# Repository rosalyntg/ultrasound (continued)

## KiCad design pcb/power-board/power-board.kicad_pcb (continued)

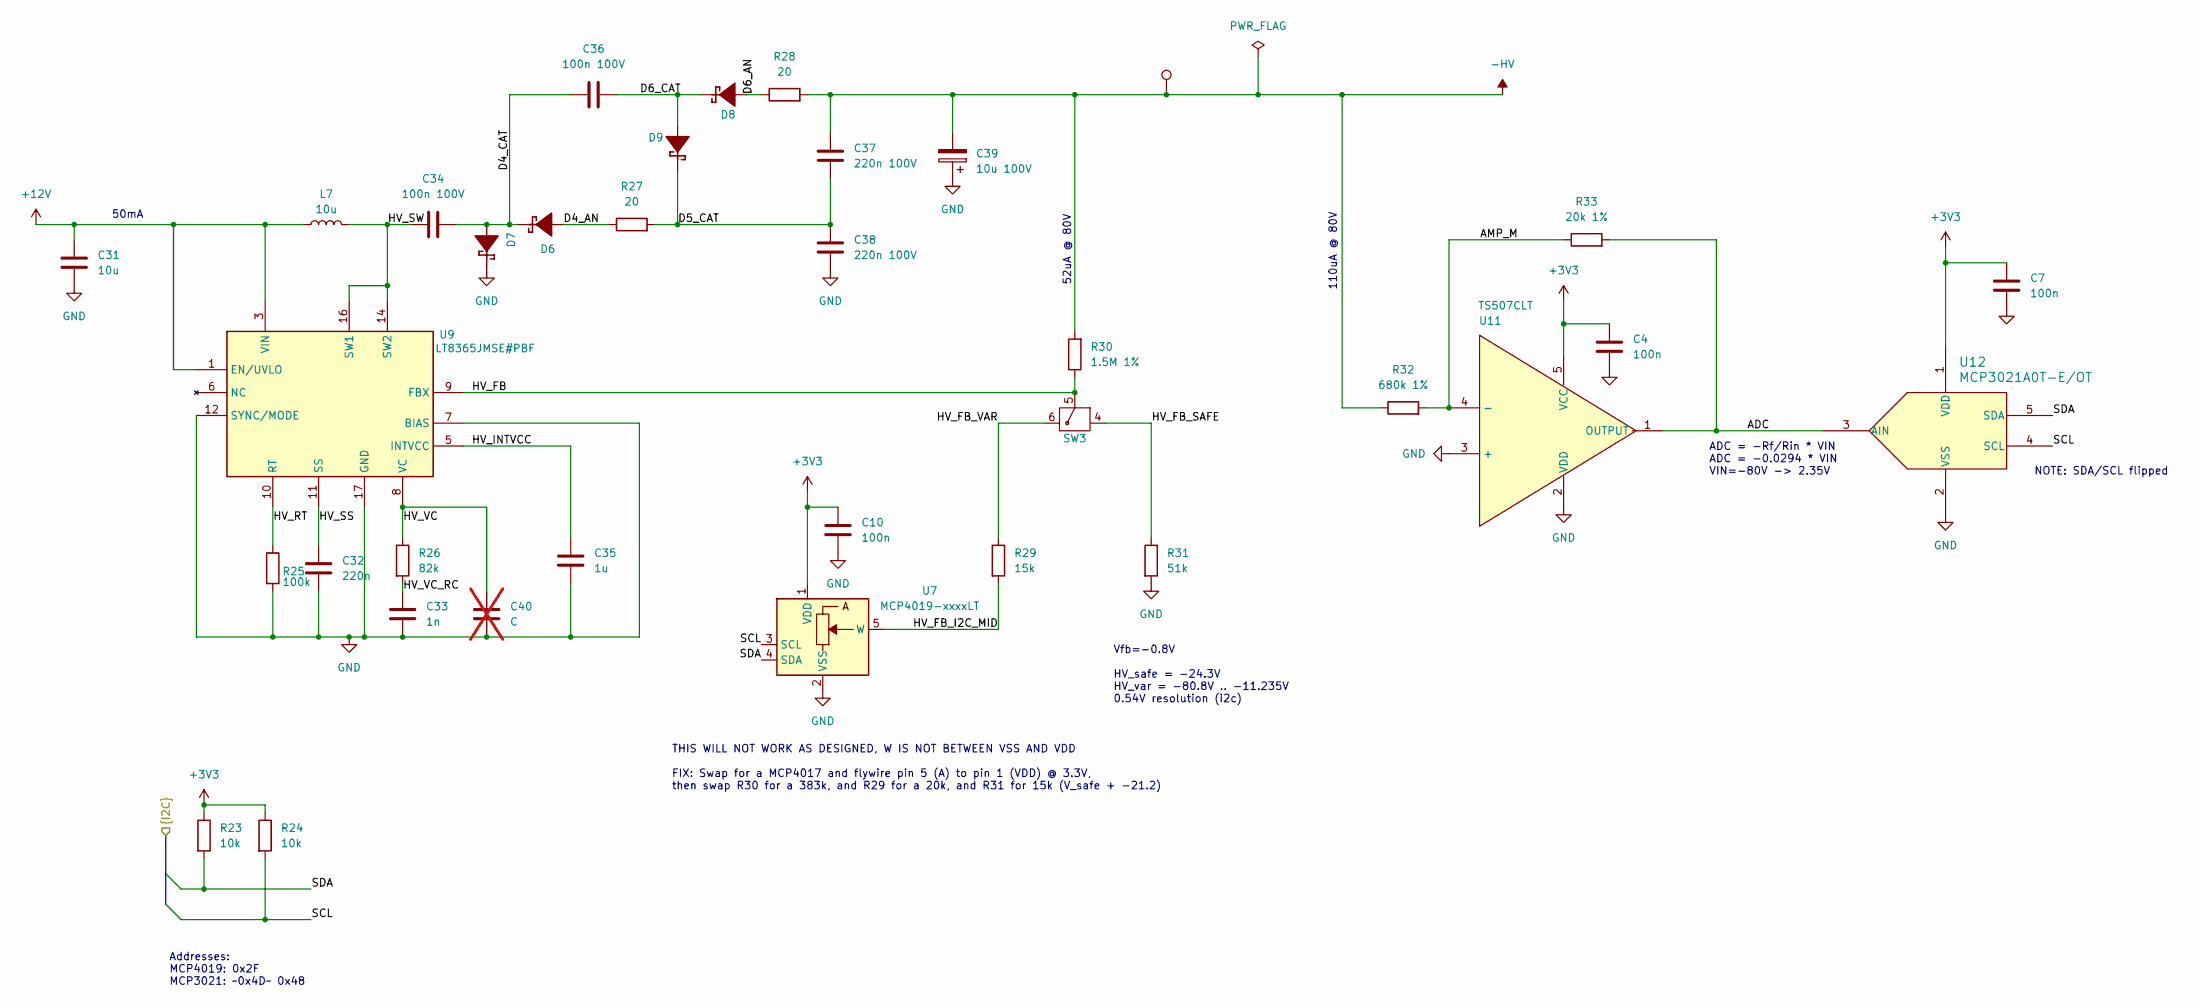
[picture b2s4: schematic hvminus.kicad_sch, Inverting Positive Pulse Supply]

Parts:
C4, C7, C10: 100n; C_0805_2012Metric_Pad1.18x1.45mm_HandSolder; Voltage Rating 25V; Manufacturer_Part_Number GCM21BR71E104KA37L; DigiKey Part Number 490-14779-1-ND
C31: 10u; C_0805_2012Metric_Pad1.18x1.45mm_HandSolder; Voltage Rating 25V; Manufacturer_Part_Number GRM21BR61E106KA73K; DigiKey Part Number 490-16824-2-ND
C32: 220n; C_0805_2012Metric_Pad1.18x1.45mm_HandSolder; Voltage Rating 25V; Manufacturer_Part_Number GRM219R71E224KA01D; DigiKey Part Number 490-1675-2-ND
C33: 1n; C_0805_2012Metric_Pad1.18x1.45mm_HandSolder; Voltage Rating 50V; Manufacturer_Part_Number GRM216R71H102KA01D
C34, C36: 100n 100V; C_0805_2012Metric_Pad1.18x1.45mm_HandSolder; Voltage Rating 100V; Manufacturer_Part_Number GCM21BR72A104KA37L; DigiKey Part Number 490-4789-1-ND
C35: 1u; C_0805_2012Metric_Pad1.18x1.45mm_HandSolder; Voltage Rating 10V; Manufacturer_Part_Number GRM21BR71A105KA01L
C37, C38: 220n 100V; C_1210_3225Metric_Pad1.33x2.70mm_HandSolder; Voltage Rating 200V; Manufacturer_Part_Number GRM32DR72D224KW01L; DigiKey Part Number 490-13380-1-ND
C39: 10u 100V; CP_Radial_D10.0mm_P5.00mm; Voltage Rating 200V; Manufacturer_Part_Number ECA-2DHG100; DigiKey Part Number P19449-ND
C40: C; C_0805_2012Metric_Pad1.18x1.45mm_HandSolder; not fitted
D6, D7, D8, D9: SMD1150PL-TP; SMD1150PL; Voltage Rating 150V; Mouser Part Number 621-DFLS1150-7
L7: 10u; WURTH_WE-LHMI-4.45mm; Mouser Part Number 710-74437324100
R23, R24: 10k; R_0805_2012Metric_Pad1.20x1.40mm_HandSolder; Manufacturer_Part_Number RC0805JR-0710K
R25: 100k; R_0805_2012Metric_Pad1.20x1.40mm_HandSolder; Manufacturer_Part_Number RC0805JR-07100R; DigiKey Part Number 311-107KCRCT-ND
R26: 82k; R_0805_2012Metric_Pad1.20x1.40mm_HandSolder; Manufacturer_Part_Number RC0805JR-0782K
R27, R28: 20; R_0805_2012Metric_Pad1.20x1.40mm_HandSolder; Manufacturer_Part_Number RC0805JR-0720R
R29: 15k; R_0805_2012Metric_Pad1.20x1.40mm_HandSolder; Manufacturer_Part_Number RC0805FR-0712KL; DigiKey Part Number RC0805JR-0715K
R30: 1.5M 1%; R_0805_2012Metric_Pad1.20x1.40mm_HandSolder; Manufacturer_Part_Number RT0805BRD071M5L; DigiKey Part Number 13-RT0805BRD071M5LCT-ND
R31: 51k; R_0805_2012Metric_Pad1.20x1.40mm_HandSolder; Manufacturer_Part_Number RC0805JR-0751K
R32: 680k 1%; R_0805_2012Metric_Pad1.20x1.40mm_HandSolder; Manufacturer_Part_Number RC0805FR-07680KL; DigiKey Part Number 311-680KCRCT-ND
R33: 20k 1%; R_0805_2012Metric_Pad1.20x1.40mm_HandSolder; Manufacturer_Part_Number RC0805FR-0720KL; DigiKey Part Number 311-20.0KCRCT-ND
SW3: CST11T2CR; Manufacturer_Part_Number CST11T2CR; DigiKey Part Number 2449-CST11T2CR-ND
TP11: TestPoint; TestPoint_THTPad_2.5x2.5mm_Drill1.2mm
U7: MCP4019-xxxxLT; SOT-353_SC-70-5; Manufacturer_Part_Number MCP4019T-104E/LTCT-ND; DigiKey Part Number MCP4019T-104E/LT
U9: LT8365JMSE#PBF; LT8365JMSEPBF; Mouser Part Number 584-LT8365JMSE#PBF
U11: TS507CLT; SOT95P280X145-5N; Manufacturer_Part_Number TS507CLT; Mouser Part Number 511-TS507CLT
U12: MCP3021A0T-E/OT; SOT-23-5_MC_MCH-M; Manufacturer_Part_Number MCP3021A0T-E/OT; DigiKey Part Number MCP3021A0T-E/OTCT-ND

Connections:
+3V3: C4.1, C7.1, C10.1, R23.1, R24.1, U7.1 (VDD), U11.5 (VCC), U12.1 (VDD); also elsewhere on the board
+12V: C31.1, L7.1, U9.1 (EN/UVLO), U9.3 (VIN); also elsewhere on the board
-HV: C37.1, C39.2, R28.2, R30.2, R32.1, TP11.1 (1_1); also elsewhere on the board
/HV-.SCL: R24.2, U7.3 (SCL), U12.4 (SCL); also elsewhere on the board
/HV-.SDA: R23.2, U7.4 (SDA), U12.5 (SDA); also elsewhere on the board
/HV-/ADC: R33.2, U11.1 (OUTPUT), U12.3 (AIN)
/HV-/AMP_M: R32.2, R33.1, U11.4 (-)
/HV-/D4_AN: D6.2 (A), R27.1
/HV-/D4_CAT: C34.2, C36.1, D6.1 (K), D7.2 (A)
/HV-/D5_CAT: C37.2, C38.1, D9.1 (K), R27.2
/HV-/D6_AN: D8.2 (A), R28.1
/HV-/D6_CAT: C36.2, D8.1 (K), D9.2 (A)
/HV-/HV_FB: R30.1, SW3.5, U9.9 (FBX)
/HV-/HV_FB_I2C_MID: R29.2, U7.5 (W)
/HV-/HV_FB_SAFE: R31.1, SW3.4
/HV-/HV_FB_VAR: R29.1, SW3.6
/HV-/HV_INTVCC: C35.1, U9.5 (INTVCC)
/HV-/HV_RT: R25.1, U9.10 (RT)
/HV-/HV_SS: C32.1, U9.11 (SS)
/HV-/HV_SW: C34.1, L7.2, U9.14 (SW2), U9.16 (SW1)
/HV-/HV_VC: C40.1, R26.1, U9.8 (VC)
/HV-/HV_VC_RC: C33.1, R26.2
GND: C4.2, C7.2, C10.2, C31.2, C32.2, C33.2, C35.2, C38.2, C39.1, C40.2, D7.1 (K), R25.2, R31.2, U7.2 (VSS), U9.7 (BIAS), U9.12 (SYNC/MODE), U9.17 (GND), U11.2 (VDD), U11.3 (+), U12.2 (VSS); also elsewhere on the board

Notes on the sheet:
THIS WILL NOT WORK AS DESIGNED, W IS NOT BETWEEN VSS AND VDD FIX: Swap for a MCP4017 and flywire pin 5 (A) to pin 1 (VDD) @ 3.3V, then swap R30 for a 383k, and R29 for a 20k, and R31 for 15k (V_safe + -21.2)
110uA @ 80V
NOTE: SDA/SCL flipped
Addresses: MCP4019: 0x2F MCP3021: ~0x4D~ 0x48
ADC = -Rf/Rin * VIN ADC = -0.0294 * VIN VIN=-80V -> 2.35V
50mA
52uA @ 80V
Vfb=-0.8V HV_safe = -24.3V HV_var = -80.8V .. -11.235V 0.54V resolution (i2c)

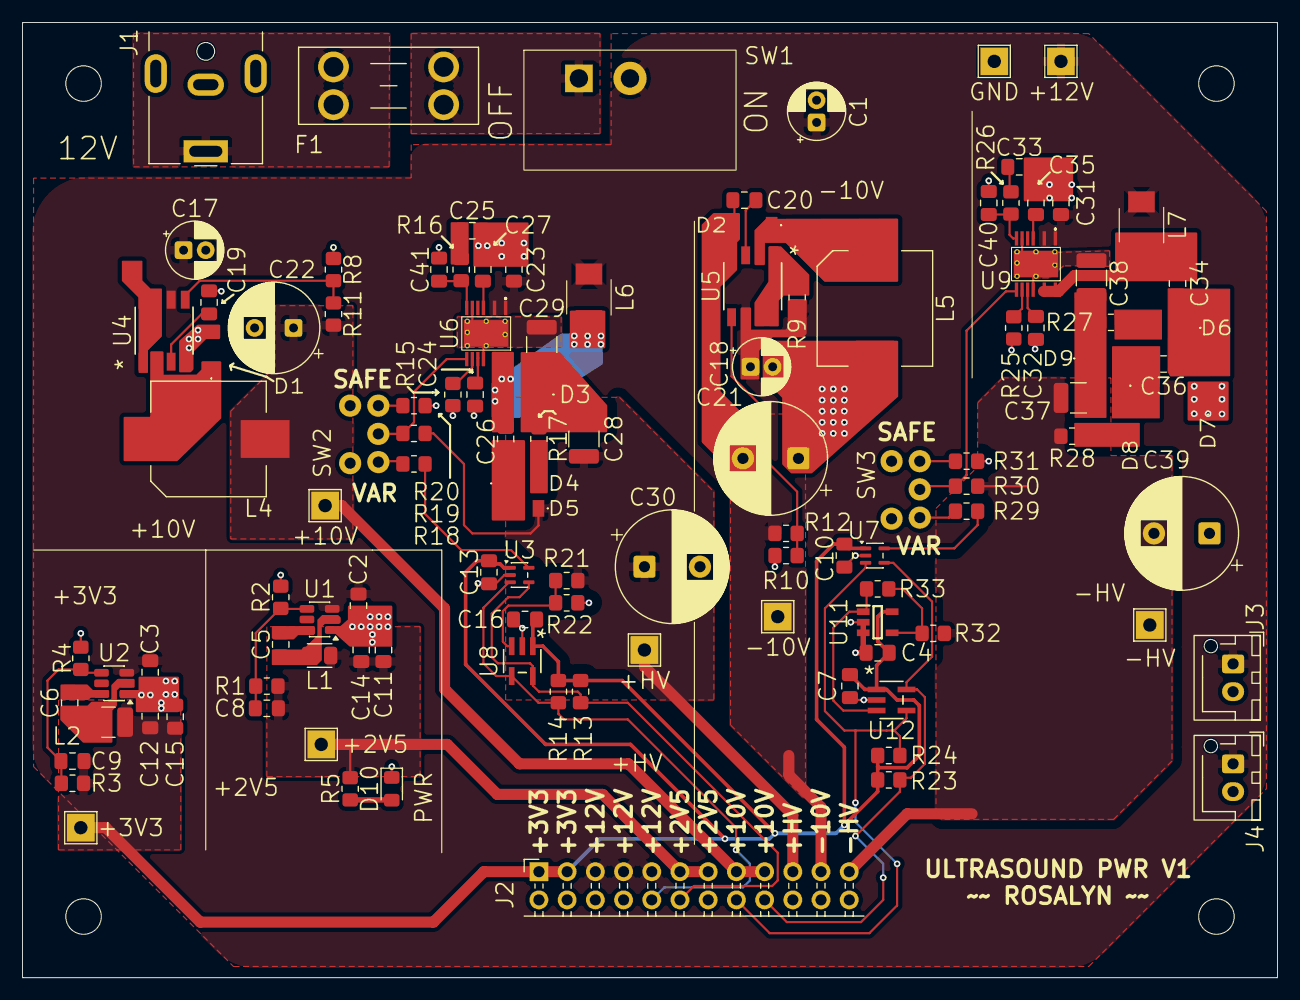
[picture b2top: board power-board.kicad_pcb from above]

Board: 2 copper layers, 113.0 x 86.0 mm, 120 parts (1 on the bottom side), 60 nets.

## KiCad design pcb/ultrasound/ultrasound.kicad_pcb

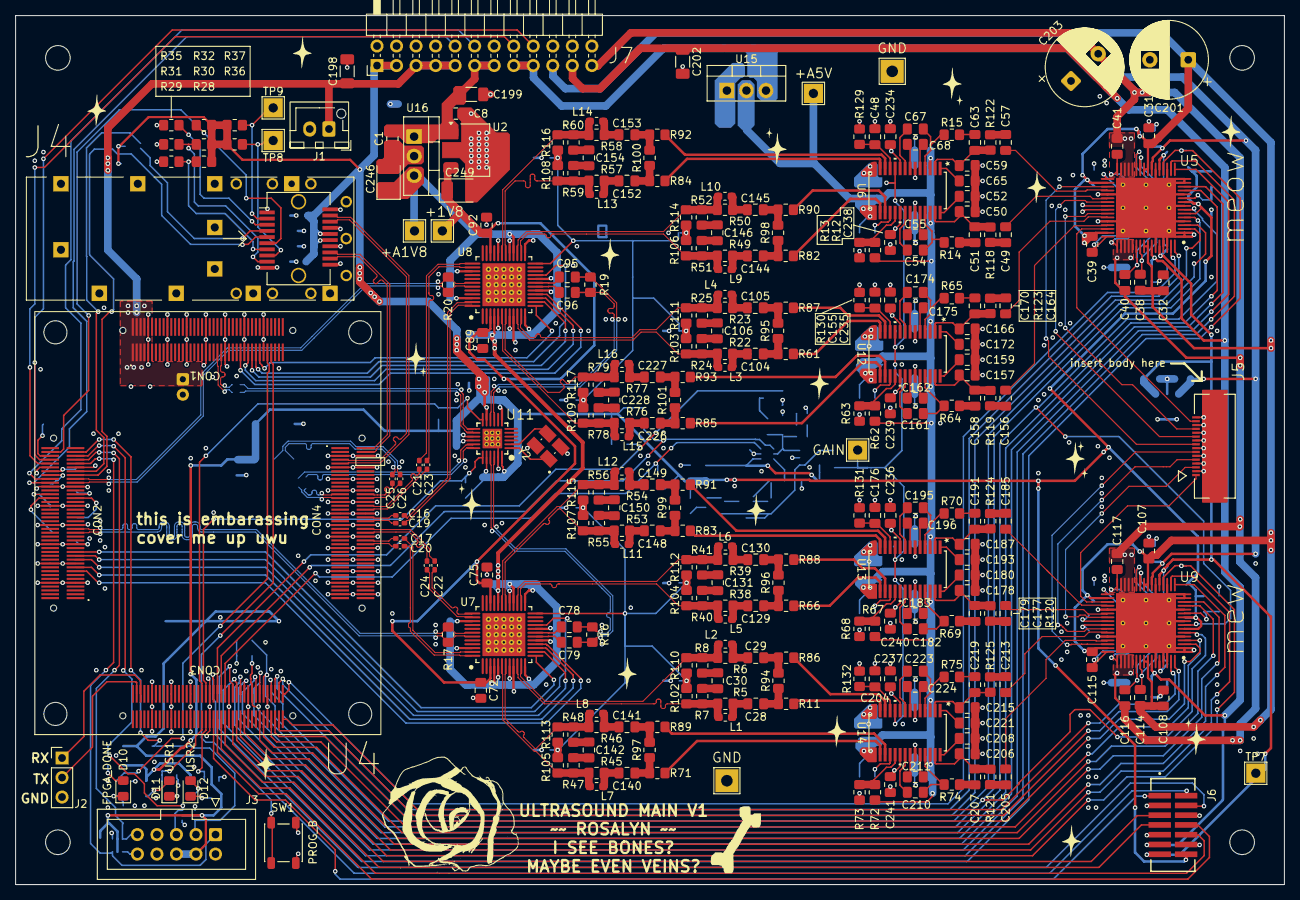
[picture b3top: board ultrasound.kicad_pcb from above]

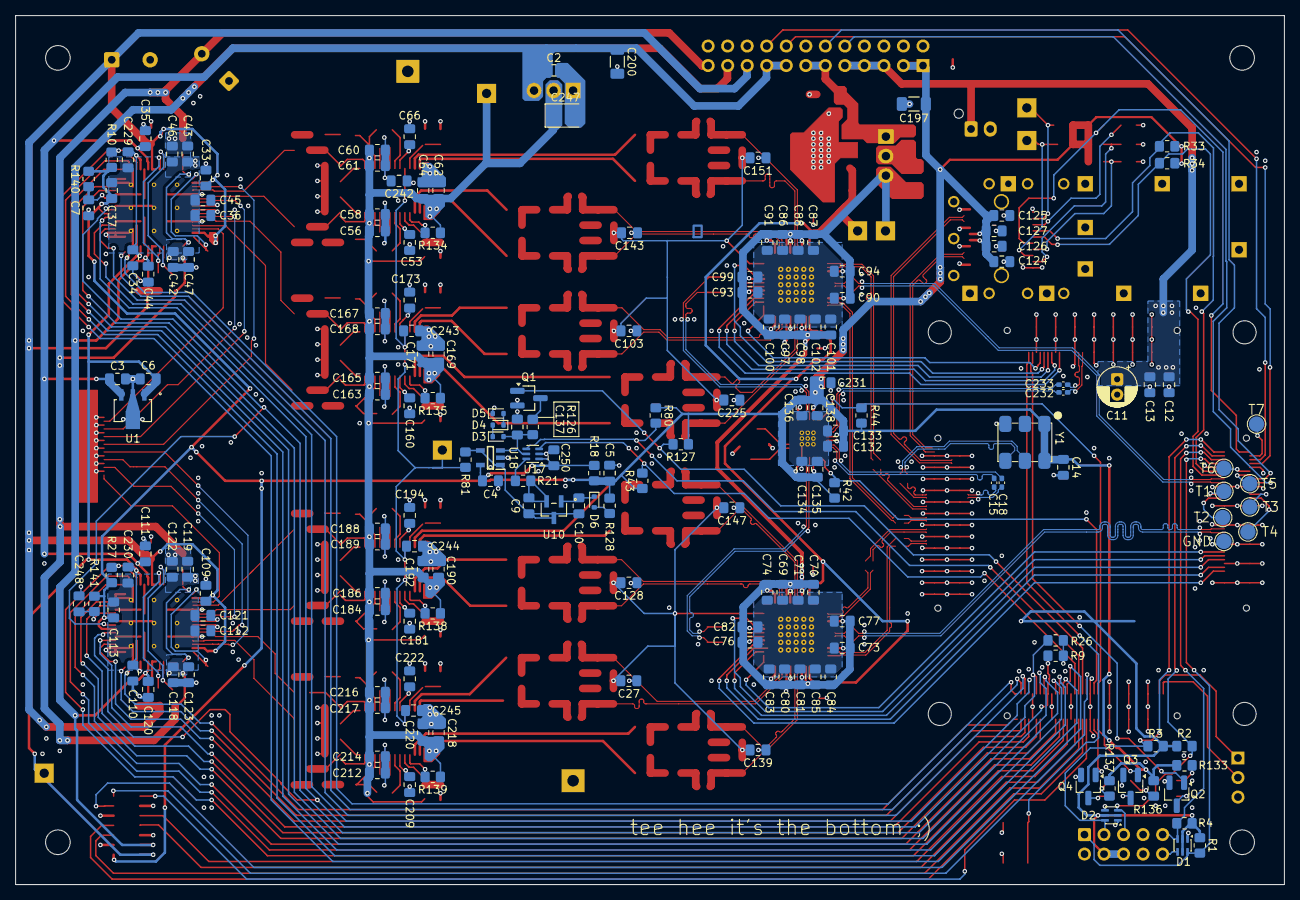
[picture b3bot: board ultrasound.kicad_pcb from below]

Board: 4 copper layers, 165.0 x 113.0 mm, 468 parts (179 on the bottom side), 342 nets.

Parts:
C1, C2, C8, C124, C125, C231: 10u; C_0805_2012Metric_Pad1.18x1.45mm_HandSolder
C3: 330n; C_0805_2012Metric_Pad1.18x1.45mm_HandSolder
C4, C6, C14, C27, C28, C29, C48, C49, C52, C53, C54, C55, C56, C57, C60, C62, C65, C66, C67, C68, C69, C70, C71, C72, C73, C74, C75, C76, C77, C78, C79, C80, C81, C82, C83, C84, C85, C86, C87, C88, C89, C90, C91, C92, C93, C94, C95, C96, C97, C98, C99, C100, C101, C102, C103, C104, C105, C126, C127, C128, C129, C130, C132, C133, C134, C135, C136, C138, C139, C140, C141, C143, C144, C145, C147, C148, C149, C151, C152, C153, C155, C156, C159, C160, C161, C162, C163, C164, C167, C169, C172, C173, C174, C175, C176, C177, C180, C181, C182, C183, C184, C185, C188, C190, C193, C194, C195, C196, C204, C205, C208, C209, C210, C211, C212, C213, C216, C218, C221, C222, C223, C224, C225, C226, C227, C250: 100n; C_0805_2012Metric_Pad1.18x1.45mm_HandSolder
C5, C7, C248: C; C_0805_2012Metric_Pad1.18x1.45mm_HandSolder
C9, C10, C36, C45, C112, C121: 1u; C_0805_2012Metric_Pad1.18x1.45mm_HandSolder
C11: 100u; CP_Radial_D5.0mm_P2.00mm
C12, C13: 22u; C_0805_2012Metric_Pad1.18x1.45mm_HandSolder
C15, C16, C17, C18, C19, C20, C21, C22, C23, C24: 100n; C_0402_1005Metric_Pad0.74x0.62mm_HandSolder
C25, C26, C232, C233: 10n; C_0402_1005Metric_Pad0.74x0.62mm_HandSolder
C30, C50, C59, C106, C131, C142, C146, C150, C154, C157, C166, C178, C187, C206, C215, C228: 22p; C_0805_2012Metric_Pad1.18x1.45mm_HandSolder
C31, C32, C33, C107, C108, C109: 2.2u 100V; C_0805_2012Metric_Pad1.18x1.45mm_HandSolder
C34, C35, C37, C38, C39, C40, C41, C44, C110, C111, C113, C114, C115, C116, C117, C120, C229, C230: 2.2u; C_0805_2012Metric_Pad1.18x1.45mm_HandSolder
C42, C43, C46, C47, C118, C119, C122, C123: 1u 100V; C_0805_2012Metric_Pad1.18x1.45mm_HandSolder
C51, C63, C158, C170, C179, C191, C207, C219: 18n; C_0805_2012Metric_Pad1.18x1.45mm_HandSolder
C58, C61, C64, C165, C168, C171, C186, C189, C192, C214, C217, C220, C234, C235, C236, C237, C238, C239, C240, C241, C242, C243, C244, C245: 1n; C_0805_2012Metric_Pad1.18x1.45mm_HandSolder
C137: 3n; C_0805_2012Metric_Pad1.18x1.45mm_HandSolder
C197, C198, C199, C200, C202: 100u; C_1206_3216Metric_Pad1.33x1.80mm_HandSolder
C201, C203: 10u 100V; CP_Radial_D10.0mm_P5.00mm
C246, C247, C249: 47u Tantalum; CP_EIA-3528-15_AVX-H_HandSolder
D1, D2: BAT54SDW; SOT-363_SC-70-6
D3, D4, D5, D6: 1N914WT; D_SOD-523
D10, D11, D12: LED; LED_0805_2012Metric_Pad1.15x1.40mm_HandSolder
H1, H2, H3, H4: MountingHole; MountingHole_3.2mm_M3
J1: B2B-XH-A; JST_XH_B2B-XH-AM_1x02_P2.50mm_Vertical
J2: Conn_01x03; PinHeader_1x03_P2.54mm_Vertical
J3: AVR-JTAG-10; IDC-Header_2x05_P2.54mm_Vertical
J4: UE76A202000T; Connector_SFP_and_Cage
J5: 5051101692; CON_5051101692_MOL
J6: Conn_02x07_Counter_Clockwise; SAMTEC_TFM-107-02-L-D
J7: Conn_02x12_Odd_Even; PinHeader_2x12_P2.54mm_Horizontal
L1, L2, L3, L4, L5, L6, L7, L8, L9, L10, L11, L12, L13, L14, L15, L16: 39n; L_0603_1608Metric_Pad1.05x0.95mm_HandSolder
Q1, Q2, Q3, Q4: BS170F; SOT-23_Handsoldering
R1, R2, R3, R4, R21, R26, R32, R33, R34, R42, R43, R44, R80, R127: 10k; R_0805_2012Metric_Pad1.20x1.40mm_HandSolder
R5, R6, R9, R12, R13, R18, R22, R23, R38, R39, R45, R46, R49, R50, R53, R54, R57, R58, R62, R63, R67, R68, R72, R73, R76, R77, R118, R119, R120, R121, R122, R123, R124, R125, R140, R141: 0; R_0805_2012Metric_Pad1.20x1.40mm_HandSolder
R7, R8, R24, R25, R40, R41, R47, R48, R51, R52, R55, R56, R59, R60, R78, R79: 150; R_0805_2012Metric_Pad1.20x1.40mm_HandSolder
R10, R27: 100k; R_0805_2012Metric_Pad1.20x1.40mm_HandSolder
R11, R61, R66, R71, R82, R83, R84, R85, R86, R87, R88, R89, R90, R91, R92, R93, R133, R136, R137: 68; R_0805_2012Metric_Pad1.20x1.40mm_HandSolder
R14, R15, R64, R65, R69, R70, R74, R75: 280 1%; R_0805_2012Metric_Pad1.20x1.40mm_HandSolder
R16, R17, R19, R20: 100 1%; R_0805_2012Metric_Pad1.20x1.40mm_HandSolder
R28, R29, R30, R31, R35: R; R_0805_2012Metric_Pad1.20x1.40mm_HandSolder
R36, R37: 4.3k; R_0805_2012Metric_Pad1.20x1.40mm_HandSolder
R81: 500; R_0805_2012Metric_Pad1.20x1.40mm_HandSolder
R94, R95, R96, R97, R98, R99, R100, R101: 374; R_0805_2012Metric_Pad1.20x1.40mm_HandSolder
R102, R103, R104, R105, R106, R107, R108, R109, R110, R111, R112, R113, R114, R115, R116, R117: 1k; R_0805_2012Metric_Pad1.20x1.40mm_HandSolder
R126: 200; R_0805_2012Metric_Pad1.20x1.40mm_HandSolder
R128: 510; R_0805_2012Metric_Pad1.20x1.40mm_HandSolder
R129, R130, R131, R132: 6.8k; R_0805_2012Metric_Pad1.20x1.40mm_HandSolder
R134, R135, R138, R139: 5.1k; R_0805_2012Metric_Pad1.20x1.40mm_HandSolder
SW1: SW_SPST; SW_SPST_PTS647_Sx38
TP1, TP2, TP3, TP5, TP7, TP8, TP9: TestPoint; TestPoint_THTPad_2.5x2.5mm_Drill1.2mm
TP4, TP6: TestPoint; TestPoint_THTPad_3.0x3.0mm_Drill1.5mm
TP10, TP11, TP12, TP13, TP14, TP15, TP16, TP17: TestPoint; TestPoint_Pad_D2.0mm
U1: AS78L05RTR-E1; SOT89_B8D_DIO-M
U2: MCP1755ST; SOT-223-3_TabPin2
U4: AXAU15; AXAU15_CLIP
U5, U9: HV7321K6-G; QFN50P900X900X100-65N-D
U6, U12, U13, U14: AD8332ARUZ; RU_28_ADI-M
U7, U8: ADC34J22IRGZ25; RGZ0048D_TEX
U10: MAX6018BEUR12+T; 21-0051H_MXM-M
U11: SI5338Q-B-GM; SI5338QBGM
U15: LM1085IT-5.0; TO-220-3_Vertical
U16: MIC39300-1.8WT; TO-220-3_Vertical
U17: MCP4017-103E/LTY; SOT-363_SC-70-6
U18: TS507CLT; SOT95P280X145-5N
Y1: SIT9121AC-2D2-33E156.250000; Oscillator_SMD_SiTime_PQFD-6L_7x5mm
Y2: FA-238 25.0000MB-C3; XTAL_FA-238_25.0000MB50X-C0

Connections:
+1V8: C72.1, C75.1, C89.1, C92.1, C249.1, D1.2 (K), D1.5 (K), D2.2 (K), D2.5 (K), J3.4 (VREF), J3.6 (~SRST), R1.1, R2.1, R3.1, R4.1, TP5.1 (1_1), U2.3 (VO), U7.3 (DVDD), U7.34 (DVDD), U8.3 (DVDD), U8.34 (DVDD)
+2V5: C1.1, C8.1, C199.1, J7.11, J7.13, U2.1 (VI), U16.1 (IN)
+3V3: C5.1, C14.1, C37.1, C113.1, C124.1, C125.1, C126.1, C127.1, C132.1, C133.1, C134.1, C135.1, C136.1, C138.1, C197.1, C231.1, J4.15 (VccR), J4.16 (VccT), J6.14, J7.1, J7.3, R10.1, R18.2, R27.1, R28.1, R30.1, R32.1, R33.1, R34.1, R36.1, R37.1, R42.1, R43.1, R44.1, R80.1, R127.1, R128.2, R133.1, R136.1, R137.1, R140.1, R141.1, U5.7 (PWS), U5.10 (VLL), U9.7 (PWS), U9.10 (VLL), U11.7 (VDD_1), U11.11 (VDDO3), U11.15 (VDDO2), U11.16 (VDDO1), U11.20 (VDDO0), U11.24 (VDD_2), Y1.1 (OE), Y1.6 (VDD)
+5V: C6.1, C34.1, C110.1, C229.1, C230.1, J6.13, TP7.1 (1_1), U1.1 (OUTPUT), U5.21 (VDD_1), U5.60 (VDD_2), U9.21 (VDD_1), U9.60 (VDD_2)
+10V: C2.1, C3.1, C35.1, C111.1, C200.1, J7.15, J7.17, U1.3 (INPUT), U5.23 (VGP), U9.23 (VGP), U15.3 (IN)
+12V: C11.1, C12.1, C13.1, C198.1, J1.1, J7.5, J7.7, J7.9, U4.1x1 (VCCIN), U4.1x2 (VCCIN), U4.1x3 (VCCIN), U4.1x4 (VCCIN), U4.1x5 (VCCIN), U4.1x6 (VCCIN), U4.1x7 (VCCIN), U4.1x8 (VCCIN)
+A1V8: C69.1, C70.1, C71.1, C73.1, C74.1, C76.1, C77.1, C80.1, C81.1, C82.1, C83.1, C84.1, C85.1, C86.1, C87.1, C88.1, C90.1, C91.1, C93.1, C94.1, C97.1, C98.1, C99.1, C100.1, C101.1, C102.1, C246.1, TP1.1 (1_1), U7.4 (AVDD), U7.5 (AVDD), U7.8 (AVDD), U7.9 (AVDD), U7.12 (AVDD), U7.17 (AVDD), U7.20 (AVDD), U7.25 (AVDD), U7.28 (AVDD), U7.29 (AVDD), U7.32 (AVDD), U7.39 (AVDD), U7.46 (AVDD), U8.4 (AVDD), U8.5 (AVDD), U8.8 (AVDD), U8.9 (AVDD), U8.12 (AVDD), U8.17 (AVDD), U8.20 (AVDD), U8.25 (AVDD), U8.28 (AVDD), U8.29 (AVDD), U8.32 (AVDD), U8.39 (AVDD), U8.46 (AVDD), U16.3 (OUT)
+A5V: C56.1, C58.1, C60.1, C61.1, C62.1, C64.1, C163.1, C165.1, C167.1, C168.1, C169.1, C171.1, C184.1, C186.1, C188.1, C189.1, C190.1, C192.1, C212.1, C214.1, C216.1, C217.1, C218.1, C220.1, C247.1, R12.1, R62.1, R67.1, R72.1, R134.1, R135.1, R138.1, R139.1, TP2.1 (1_1), U6.3 (VPS2), U6.15 (VPSV), U6.26 (VPS1), U12.3 (VPS2), U12.15 (VPSV), U12.26 (VPS1), U13.3 (VPS2), U13.15 (VPSV), U13.26 (VPS1), U14.3 (VPS2), U14.15 (VPSV), U14.26 (VPS1), U15.2 (OUT)
+HV: C31.1, C32.1, C33.1, C38.1, C39.1, C107.1, C108.1, C109.1, C114.1, C115.1, C201.1, J7.19, U5.24 (VPP0_1), U5.25 (VPP0_2), U5.34 (VPP1_1), U5.47 (VPP1_2), U5.56 (VPP0_3), U5.57 (VPP0_4), U9.24 (VPP0_1), U9.25 (VPP0_2), U9.34 (VPP1_1), U9.47 (VPP1_2), U9.56 (VPP0_3), U9.57 (VPP0_4)
-10V: C44.1, C120.1, C202.1, J6.11, J7.21, U5.58 (VGN), U9.58 (VGN)
-HV: C40.1, C41.1, C42.1, C43.1, C46.1, C47.1, C116.1, C117.1, C118.1, C119.1, C122.1, C123.1, C203.2, J7.23, U5.28 (VNN0_1), U5.29 (VNN0_2), U5.30 (VNN2_1), U5.31 (VNN1_1), U5.50 (VNN1_2), U5.51 (VNN2_2), U5.52 (VNN0_3), U5.53 (VNN0_4), U9.28 (VNN0_1), U9.29 (VNN0_2), U9.30 (VNN2_1), U9.31 (VNN1_1), U9.50 (VNN1_2), U9.51 (VNN2_2), U9.52 (VNN0_3), U9.53 (VNN0_4)
/ADC0/AC_COUP1/FILTN: C154.2, R60.1
/ADC0/AC_COUP1/FILTP: C154.1, R59.2
/ADC0/AC_COUP1/IN_ATT_N: C153.1, R92.2, R100.2
/ADC0/AC_COUP1/IN_ATT_P: C152.1, R84.2, R100.1
/ADC0/AC_COUP1/OUTN: L14.1, R58.2, R60.2, R116.2, U8.31 (INDM)
/ADC0/AC_COUP1/OUTP: L13.2, R57.2, R59.1, R108.1, U8.30 (INDP)
/ADC0/AC_COUP1/PRN: C153.2, L14.2, R58.1
/ADC0/AC_COUP1/PRP: C152.2, L13.1, R57.1
/ADC0/AC_COUP2/FILTN: C146.2, R52.1
/ADC0/AC_COUP2/FILTP: C146.1, R51.2
/ADC0/AC_COUP2/IN_ATT_N: C145.1, R90.2, R98.2
/ADC0/AC_COUP2/IN_ATT_P: C144.1, R82.2, R98.1
/ADC0/AC_COUP2/OUTN: L10.1, R50.2, R52.2, R114.2, U8.27 (INCP)
/ADC0/AC_COUP2/OUTP: L9.2, R49.2, R51.1, R106.1, U8.26 (INCM)
/ADC0/AC_COUP2/PRN: C145.2, L10.2, R50.1
/ADC0/AC_COUP2/PRP: C144.2, L9.1, R49.1
/ADC0/AC_COUP3/FILTN: C106.2, R25.1
/ADC0/AC_COUP3/FILTP: C106.1, R24.2
/ADC0/AC_COUP3/IN_ATT_N: C105.1, R87.2, R95.2
/ADC0/AC_COUP3/IN_ATT_P: C104.1, R61.2, R95.1
/ADC0/AC_COUP3/OUTN: L4.1, R23.2, R25.2, R111.2, U8.11 (INBM)
/ADC0/AC_COUP3/OUTP: L3.2, R22.2, R24.1, R103.1, U8.10 (INBP)
/ADC0/AC_COUP3/PRN: C105.2, L4.2, R23.1
/ADC0/AC_COUP3/PRP: C104.2, L3.1, R22.1
/ADC0/AC_COUP4/FILTN: C228.2, R79.1
/ADC0/AC_COUP4/FILTP: C228.1, R78.2
/ADC0/AC_COUP4/IN_ATT_N: C227.1, R93.2, R101.2
/ADC0/AC_COUP4/IN_ATT_P: C226.1, R85.2, R101.1
/ADC0/AC_COUP4/OUTN: L16.1, R77.2, R79.2, R117.2, U8.7 (INAP)
/ADC0/AC_COUP4/OUTP: L15.2, R76.2, R78.1, R109.1, U8.6 (INAM)
/ADC0/AC_COUP4/PRN: C227.2, L16.2, R77.1
/ADC0/AC_COUP4/PRP: C226.2, L15.1, R76.1
/ADC0/CLK.N: C96.1, R19.1, U11.10 (CLK3A)
/ADC0/CLK.P: C95.1, R19.2, U11.9 (CLK3B)
/ADC0/CLK_AC_N: C96.2, U8.18 (CLKM)
/ADC0/CLK_AC_P: C95.2, U8.19 (CLKP)
/ADC0/DAN: C19.1, U8.48 (DAM)
/ADC0/DAP: C16.1, U8.47 (DAP)
/ADC0/DDN: C23.1, U8.38 (DDM)
/ADC0/DDP: C21.1, U8.37 (DDP)
/ADC0/IN1.N: R84.1, U6.13 (VOL2)
/ADC0/IN1.P: R92.1, U6.12 (VOH2)
/ADC0/IN2.N: R82.1, U6.16 (VOL1)
/ADC0/IN2.P: R90.1, U6.17 (VOH1)
/ADC0/IN3.N: R61.1, U12.13 (VOL2)
/ADC0/IN3.P: R87.1, U12.12 (VOH2)
/ADC0/IN4.N: R85.1, U12.16 (VOL1)
/ADC0/IN4.P: R93.1, U12.17 (VOH1)
/ADC0/MISO: U4.1x57 (B64_L20_P), U8.16 (SDOUT)
/ADC0/MOSI: U4.1x63 (B64_L23_P), U8.14 (SDATA)
/ADC0/RESET: U4.1x65 (B64_L18_N), U8.21 (RESET)
/ADC0/SCLK: U4.1x67 (B64_L18_P), U8.13 (SCLK)
/ADC0/SYNC.N: R20.2, U4.2x63 (B65_L1_P), U8.42 (SYNCM~)
/ADC0/SYNC.P: R20.1, U4.2x61 (B65_L1_N), U8.43 (SYNCP~)
/ADC0/VCM: C103.2, C143.2, C151.2, C225.2, R103.2, R106.2, R108.2, R109.2, R111.1, R114.1, R116.1, R117.1, U8.24 (VCM)
/ADC0/~CS: U4.1x61 (B64_L23_N), U8.15 (SEN)
/ADC1/AC_COUP1/FILTN: C150.2, R56.1
/ADC1/AC_COUP1/FILTP: C150.1, R55.2
/ADC1/AC_COUP1/IN_ATT_N: C149.1, R91.2, R99.2
/ADC1/AC_COUP1/IN_ATT_P: C148.1, R83.2, R99.1
/ADC1/AC_COUP1/OUTN: L12.1, R54.2, R56.2, R115.2, U7.31 (INDM)
/ADC1/AC_COUP1/OUTP: L11.2, R53.2, R55.1, R107.1, U7.30 (INDP)
/ADC1/AC_COUP1/PRN: C149.2, L12.2, R54.1
/ADC1/AC_COUP1/PRP: C148.2, L11.1, R53.1
/ADC1/AC_COUP2/FILTN: C131.2, R41.1
/ADC1/AC_COUP2/FILTP: C131.1, R40.2
/ADC1/AC_COUP2/IN_ATT_N: C130.1, R88.2, R96.2
/ADC1/AC_COUP2/IN_ATT_P: C129.1, R66.2, R96.1
/ADC1/AC_COUP2/OUTN: L6.1, R39.2, R41.2, R112.2, U7.27 (INCP)
/ADC1/AC_COUP2/OUTP: L5.2, R38.2, R40.1, R104.1, U7.26 (INCM)
/ADC1/AC_COUP2/PRN: C130.2, L6.2, R39.1
/ADC1/AC_COUP2/PRP: C129.2, L5.1, R38.1
/ADC1/AC_COUP3/FILTN: C30.2, R8.1
/ADC1/AC_COUP3/FILTP: C30.1, R7.2
/ADC1/AC_COUP3/IN_ATT_N: C29.1, R86.2, R94.2
/ADC1/AC_COUP3/IN_ATT_P: C28.1, R11.2, R94.1
/ADC1/AC_COUP3/OUTN: L2.1, R6.2, R8.2, R110.2, U7.11 (INBM)
/ADC1/AC_COUP3/OUTP: L1.2, R5.2, R7.1, R102.1, U7.10 (INBP)
/ADC1/AC_COUP3/PRN: C29.2, L2.2, R6.1
/ADC1/AC_COUP3/PRP: C28.2, L1.1, R5.1
/ADC1/AC_COUP4/FILTN: C142.2, R48.1
/ADC1/AC_COUP4/FILTP: C142.1, R47.2
/ADC1/AC_COUP4/IN_ATT_N: C141.1, R89.2, R97.2
/ADC1/AC_COUP4/IN_ATT_P: C140.1, R71.2, R97.1
/ADC1/AC_COUP4/OUTN: L8.1, R46.2, R48.2, R113.2, U7.7 (INAP)
/ADC1/AC_COUP4/OUTP: L7.2, R45.2, R47.1, R105.1, U7.6 (INAM)
/ADC1/AC_COUP4/PRN: C141.2, L8.2, R46.1
/ADC1/AC_COUP4/PRP: C140.2, L7.1, R45.1
/ADC1/CLK.N: C79.1, R16.1, U11.22 (CLK0A)
/ADC1/CLK.P: C78.1, R16.2, U11.21 (CLK0B)
/ADC1/CLK_AC_N: C79.2, U7.18 (CLKM)
/ADC1/CLK_AC_P: C78.2, U7.19 (CLKP)
/ADC1/DAN: C20.1, U7.48 (DAM)
/ADC1/DAP: C17.1, U7.47 (DAP)
/ADC1/DDN: C24.1, U7.38 (DDM)
/ADC1/DDP: C22.1, U7.37 (DDP)
/ADC1/IN1.N: R83.1, U13.13 (VOL2)
/ADC1/IN1.P: R91.1, U13.12 (VOH2)
/ADC1/IN2.N: R66.1, U13.16 (VOL1)
/ADC1/IN2.P: R88.1, U13.17 (VOH1)
/ADC1/IN3.N: R11.1, U14.13 (VOL2)
/ADC1/IN3.P: R86.1, U14.12 (VOH2)
/ADC1/IN4.N: R71.1, U14.16 (VOL1)
/ADC1/IN4.P: R89.1, U14.17 (VOH1)
/ADC1/MISO: U4.2x15 (B65_L17_N), U7.16 (SDOUT)
/ADC1/MOSI: U4.2x21 (B65_L16_N), U7.14 (SDATA)
/ADC1/RESET: U4.2x23 (B65_L16_P), U7.21 (RESET)
/ADC1/SCLK: U4.2x25 (B65_L10_N), U7.13 (SCLK)
/ADC1/SYNC.N: R17.2, U4.2x37 (B65_L2_P), U7.42 (SYNCM~)
/ADC1/SYNC.P: R17.1, U4.2x35 (B65_L2_N), U7.43 (SYNCP~)
/ADC1/VCM: C27.2, C128.2, C139.2, C147.2, R102.2, R104.2, R105.2, R107.2, R110.1, R112.1, R113.1, R115.1, U7.24 (VCM)
/ADC1/~CS: U4.2x17 (B65_L17_P), U7.15 (SEN)
/CLK/CLKINN: U11.1 (IN1), Y2.1
/CLK/CLKINP: U11.2 (IN2), Y2.3
/CLK/OUT1.N: C15.1, U11.18 (CLK1A)
/CLK/OUT1.P: C18.1, U11.17 (CLK1B)
/CLK/OUT2.N: C232.2, U11.14 (CLK2A)
/CLK/OUT2.P: C233.2, U11.13 (CLK2B)
/CLK/SCL: R44.2, U4.3x43 (B85_L8_P), U11.12 (SCL)
/CLK/SDA: R42.2, U4.3x41 (B85_L8_N), U11.19 (SDA)
/FPGA/ADC0_A_MGT_N: C16.2, U4.4x38 (225_RX1_N)
/FPGA/ADC0_A_MGT_P: C19.2, U4.4x40 (225_RX1_P)
/FPGA/ADC0_D_MGT_N: C21.2, U4.4x32 (225_RX0_N)
/FPGA/ADC0_D_MGT_P: C23.2, U4.4x34 (225_RX0_P)
/FPGA/ADC1_A_MGT_N: C17.2, U4.4x50 (225_RX3_N)
/FPGA/ADC1_A_MGT_P: C20.2, U4.4x52 (225_RX3_P)
/FPGA/ADC1_D_MGT_N: C24.2, U4.4x46 (225_RX2_P)
/FPGA/ADC1_D_MGT_P: C22.2, U4.4x44 (225_RX2_N)
/FPGA/DONE_LED_AN: D10.2 (A), R133.2
/FPGA/DONE_LED_CAT: D10.1 (K), Q2.3 (D)
/FPGA/ETH_REFCLKN: C26.1, Y1.5 (OUT-)
/FPGA/ETH_REFCLKP: C25.1, Y1.4 (OUT+)
/FPGA/ETH_REFCLK_MGT_N: C25.2, U4.4x26 (224_CLK0_N)
/FPGA/ETH_REFCLK_MGT_P: C26.2, U4.4x28 (224_CLK0_P)
/FPGA/FPGA_DONE: Q2.1 (G), U4.1x71 (FPGA_DONE)
/FPGA/HV+.SCL: J7.10, U4.2x62 (B84_L2_N)
/FPGA/HV+.SDA: J7.12, U4.2x64 (B84_L2_P)
/FPGA/HV-.SCL: J7.16, U4.2x72 (B84_L3_N)
/FPGA/HV-.SDA: J7.18, U4.2x74 (B84_L3_P)
/FPGA/JESD_CORECLK_AC_N: C232.1, U4.1x45 (B64_L14_N)
/FPGA/JESD_CORECLK_AC_P: C233.1, U4.1x47 (B64_L14_P)
/FPGA/JESD_REFCLK_MGT_N: C15.2, U4.4x25 (225_CLK0_N)
/FPGA/JESD_REFCLK_MGT_P: C18.2, U4.4x27 (225_CLK0_P)
/FPGA/P0.NEG1: U4.3x21 (B85_L1_N), U5.17 (NEG3)
/FPGA/P0.NEG2: U4.3x13 (B84_L7_P), U5.13 (NEG2)
/FPGA/P0.NEG3: U4.3x5 (B84_L12_N), U5.3 (NEG1)
/FPGA/P0.NEG4: U4.3x1 (B84_L8_N), U5.63 (NEG0)
/FPGA/P0.POS1: U4.3x23 (B85_L1_P), U5.18 (POS3)
/FPGA/P0.POS2: U4.3x15 (B84_L10_N), U5.14 (POS2)
/FPGA/P0.POS3: U4.3x7 (B84_L12_P), U5.4 (POS1)
/FPGA/P0.POS4: U4.3x3 (B84_L8_P), U5.64 (POS0)
/FPGA/P0.~OTP: R10.2, U4.3x25 (B85_L2_N), U5.20 (OTPN)
/FPGA/P1.NEG1: U4.3x22 (B85_L3_N), U9.17 (NEG3)
/FPGA/P1.NEG2: U4.3x12 (B84_L9_N), U9.13 (NEG2)
/FPGA/P1.NEG3: U4.3x6 (B84_L11_N), U9.3 (NEG1)
/FPGA/P1.NEG4: U4.3x2 (B84_L5_N), U9.63 (NEG0)
/FPGA/P1.POS1: U4.3x24 (B85_L3_P), U9.18 (POS3)
/FPGA/P1.POS2: U4.3x14 (B84_L9_P), U9.14 (POS2)
/FPGA/P1.POS3: U4.3x8 (B84_L11_P), U9.4 (POS1)
/FPGA/P1.POS4: U4.3x4 (B84_L5_P), U9.64 (POS0)
/FPGA/P1.~OTP: R27.2, U4.3x26 (B85_L6_N), U9.20 (OTPN)
/FPGA/PROGRAM_B: SW1.2 (B), U4.1x73 (PROGRAM_B)
/FPGA/PULSER_CLK: R9.1, U4.3x17 (B84_L10_P), U5.8 (CLK), U9.8 (CLK)
/FPGA/PULSER_OEN: R26.1, U4.3x11 (B84_L7_N), U5.6 (OEN), U9.6 (OEN)
/FPGA/RAMP.SCL: R43.2, U4.3x31 (B85_L4_N), U17.3 (SCL)
/FPGA/RAMP.SDA: R80.2, U4.3x33 (B85_L4_P), U17.4 (SDA)
/FPGA/RAMP_RST: Q1.1 (G), R127.2, U4.3x35 (B85_L11_N)
/FPGA/S0.AUX0: J6.7, U4.3x32 (B85_L5_N)
/FPGA/S0.AUX1: J6.8, U4.3x36 (B85_L9_N)
/FPGA/S0.AUX2: J6.10, U4.3x34 (B85_L5_P)
/FPGA/S0.CLK: J6.2, U4.3x37 (B85_L11_P)
/FPGA/S0.CLR: J6.4, U4.3x27 (B85_L2_P)
/FPGA/S0.DIN: J6.5, U4.3x28 (B85_L6_P)
/FPGA/S0.~LE: J6.1, U4.3x38 (B85_L9_P)
/FPGA/SFP.SCL: J4.5 (SCL), R34.2, U4.2x65 (B84_L6_N)
/FPGA/SFP.SDA: J4.4 (SDA), R33.2, U4.2x67 (B84_L6_P)
/FPGA/SFP_MOD_ABS: J4.6 (MOD_ABS), R32.2, U4.2x78 (B84_L4_P)
/FPGA/SFP_RDN: J4.12 (RD-), U4.4x2 (224_RX0_N)
/FPGA/SFP_RDP: J4.13 (RD+), U4.4x4 (224_RX0_P)
/FPGA/SFP_TDN: J4.19 (TD-), U4.4x9 (224_TX1_P)
/FPGA/SFP_TDP: J4.18 (TD+), U4.4x7 (224_TX1_N)
/FPGA/TCK: D1.6 (K), J3.1 (TCK), R1.2, U4.2x71 (FPGA_TCK)
/FPGA/TDI: D1.3 (K), J3.9 (TDI), R4.2, U4.2x73 (FPGA_TDI)
/FPGA/TDO: D2.6 (K), J3.3 (TDO), R3.2, U4.2x77 (FPGA_TDO)
/FPGA/TEST1: TP12.1 (1_1), U4.2x55 (B65_L6_N)
/FPGA/TEST2: TP13.1 (1_1), U4.2x53 (B65_L20_P)
/FPGA/TEST3: TP10.1 (1_1), U4.2x56 (B65_L7_N)
/FPGA/TEST4: TP11.1 (1_1), U4.2x54 (B65_L9_P)
/FPGA/TEST5: TP17.1 (1_1), U4.2x66 (B84_L1_N)
/FPGA/TEST6: TP16.1 (1_1), U4.2x68 (B84_L1_P)
/FPGA/TEST7: TP15.1 (1_1), U4.2x76 (B84_L4_N)
/FPGA/TMS: D2.3 (K), J3.5 (TMS), R2.2, U4.2x75 (FPGA_TMS)
/FPGA/UART_RX: J2.1, U4.3x75 (B86_L6_N)
/FPGA/UART_TX: J2.2, U4.3x77 (B86_L6_P)
/FPGA/USRLED0: Q3.1 (G), U4.3x44 (B85_L10_P)
/FPGA/USRLED0_AN: D11.2 (A), R136.2
/FPGA/USRLED0_CAT: D11.1 (K), Q3.3 (D)
/FPGA/USRLED1: Q4.1 (G), U4.3x42 (B85_L10_N)
/FPGA/USRLED1_AN: D12.2 (A), R137.2
/FPGA/USRLED1_CAT: D12.1 (K), Q4.3 (D)
/PULSER0/CNEG: C45.1, U5.40 (CNEG)
/PULSER0/CNF0: C40.2, U5.27 (CNF0_1), U5.54 (CNF0_2)
/PULSER0/CNF1: C41.2, U5.32 (CNF1_1), U5.49 (CNF1_2)
/PULSER0/CPF0: C38.2, U5.26 (CPF0_1), U5.55 (CPF0_2)
/PULSER0/CPF1: C39.2, U5.33 (CPF1_1), U5.48 (CPF1_2)
/PULSER0/CPOS: C36.1, U5.41 (CPOS)
/PULSER0/REN: C7.1, R140.2, U5.11 (REN)
/PULSER0/TO_PIEZO1: J5.9, U5.35 (TX3)
/PULSER0/TO_PIEZO2: J5.11, U5.39 (TX2)
/PULSER0/TO_PIEZO3: J5.13, U5.42 (TX1)
/PULSER0/TO_PIEZO4: J5.15, U5.46 (TX0)
/PULSER0/TO_VGA1: C57.1, U5.36 (RX3)
/PULSER0/TO_VGA2: C49.1, U5.38 (RX2)
/PULSER0/TO_VGA3: C164.1, U5.43 (RX1)
/PULSER0/TO_VGA4: C156.1, U5.45 (RX0)
/PULSER1/CNEG: C121.1, U9.40 (CNEG)
/PULSER1/CNF0: C116.2, U9.27 (CNF0_1), U9.54 (CNF0_2)
/PULSER1/CNF1: C117.2, U9.32 (CNF1_1), U9.49 (CNF1_2)
/PULSER1/CPF0: C114.2, U9.26 (CPF0_1), U9.55 (CPF0_2)
/PULSER1/CPF1: C115.2, U9.33 (CPF1_1), U9.48 (CPF1_2)
/PULSER1/CPOS: C112.1, U9.41 (CPOS)
/PULSER1/REN: C248.1, R141.2, U9.11 (REN)
/PULSER1/TO_PIEZO1: J5.1, U9.35 (TX3)
/PULSER1/TO_PIEZO2: J5.3, U9.39 (TX2)
/PULSER1/TO_PIEZO3: J5.5, U9.42 (TX1)
/PULSER1/TO_PIEZO4: J5.7, U9.46 (TX0)
/PULSER1/TO_VGA1: C185.1, U9.36 (RX3)
/PULSER1/TO_VGA2: C177.1, U9.38 (RX2)
/PULSER1/TO_VGA3: C213.1, U9.43 (RX1)
/PULSER1/TO_VGA4: C205.1, U9.45 (RX0)
/RAMP/3V3_ISO: C4.1, C250.1, R18.1, U17.1 (VDD), U18.5 (VCC)
/RAMP/3V3_REF_R: D6.2 (A), R128.1
/RAMP/AMP_FB: C9.2, C10.2, R81.2, U10.3 (GND), U18.1 (OUTPUT), U18.4 (-)
/RAMP/DIS_D: Q1.3 (D), R126.2
/RAMP/GAIN: C242.1, C243.1, C244.1, C245.1, R81.1, TP3.1 (1_1), U6.10 (GAIN), U12.10 (GAIN), U13.10 (GAIN), U14.10 (GAIN)
/RAMP/GAIN_CLMP1: D3.1 (K), D4.2 (A)
/RAMP/GAIN_CLMP2: D4.1 (K), D5.2 (A)
/RAMP/GAIN_PREAMP: C137.1, D3.2 (A), R126.1, U17.5 (B), U18.3 (+)
/RAMP/RAMP_POT: R21.2, U17.6 (W)
/RAMP/REF_IN: C10.1, D6.1 (K), U10.1 (IN)
/RAMP/REF_OUT: C9.1, R21.1, U10.2 (OUT)
/SFP/SFP_RS0: J4.7 (RS0), R28.2, R29.1
/SFP/SFP_RS1: J4.9 (RS1), R30.2, R31.1
/SFP/SFP_RX_LOS: J4.8 (RX_LOS), R36.2, TP8.1 (1_1)
/SFP/SFP_TX_DISABLE: J4.3 (TX_DISABLE), R35.1
/SFP/SFP_TX_FAULT: J4.2 (TX_FAULT), R37.2, TP9.1 (1_1)
/VGA0/ENB: R134.2, U6.18 (ENB)
/VGA0/FB1: C51.2, R14.1
/VGA0/FB2: C63.2, R15.1
/VGA0/HI~LO: R12.2, R13.1, U6.19 (HILO)
/VGA0/IN1_AC: C49.2, R118.1
/VGA0/IN2_AC: C57.2, R122.1
/VGA0/INH1: C50.1, C51.1, R118.2, U6.27 (INH1)
/VGA0/INH2: C59.1, C63.1, R122.2, U6.2 (INH2)
/VGA0/LMD1: C52.1, U6.28 (LMD1)
/VGA0/LMD2: C65.1, U6.1 (LMD2)
/VGA0/LON1: C54.1, R14.2, U6.25 (LON1)
/VGA0/LON2: C67.1, R15.2, U6.4 (LON2)
/VGA0/LOP1: C55.1, U6.24 (LOP1)
/VGA0/LOP2: C68.1, U6.5 (LOP2)
/VGA0/RCLMP: C48.1, R129.1, U6.11 (RCLMP)
/VGA0/VCM1: C53.1, C238.1, U6.20 (VCM1)
/VGA0/VCM2: C66.1, C234.1, U6.9 (VCM2)
/VGA0/VIN1: C54.2, U6.21 (VIN1)
/VGA0/VIN2: C67.2, U6.8 (VIN2)
/VGA0/VIP1: C55.2, U6.22 (VIP1)
/VGA0/VIP2: C68.2, U6.7 (VIP2)
/VGA1/ENB: R135.2, U12.18 (ENB)
/VGA1/FB1: C158.2, R64.1
/VGA1/FB2: C170.2, R65.1
/VGA1/HI~LO: R62.2, R63.1, U12.19 (HILO)
/VGA1/IN1_AC: C156.2, R119.1
/VGA1/IN2_AC: C164.2, R123.1
/VGA1/INH1: C157.1, C158.1, R119.2, U12.27 (INH1)
/VGA1/INH2: C166.1, C170.1, R123.2, U12.2 (INH2)
/VGA1/LMD1: C159.1, U12.28 (LMD1)
/VGA1/LMD2: C172.1, U12.1 (LMD2)
/VGA1/LON1: C161.1, R64.2, U12.25 (LON1)
/VGA1/LON2: C174.1, R65.2, U12.4 (LON2)
/VGA1/LOP1: C162.1, U12.24 (LOP1)
/VGA1/LOP2: C175.1, U12.5 (LOP2)
/VGA1/RCLMP: C155.1, R130.1, U12.11 (RCLMP)
/VGA1/VCM1: C160.1, C239.1, U12.20 (VCM1)
/VGA1/VCM2: C173.1, C235.1, U12.9 (VCM2)
/VGA1/VIN1: C161.2, U12.21 (VIN1)
/VGA1/VIN2: C174.2, U12.8 (VIN2)
/VGA1/VIP1: C162.2, U12.22 (VIP1)
/VGA1/VIP2: C175.2, U12.7 (VIP2)
/VGA2/ENB: R138.2, U13.18 (ENB)
/VGA2/FB1: C179.2, R69.1
/VGA2/FB2: C191.2, R70.1
/VGA2/HI~LO: R67.2, R68.1, U13.19 (HILO)
/VGA2/IN1_AC: C177.2, R120.1
/VGA2/IN2_AC: C185.2, R124.1
/VGA2/INH1: C178.1, C179.1, R120.2, U13.27 (INH1)
/VGA2/INH2: C187.1, C191.1, R124.2, U13.2 (INH2)
/VGA2/LMD1: C180.1, U13.28 (LMD1)
/VGA2/LMD2: C193.1, U13.1 (LMD2)
/VGA2/LON1: C182.1, R69.2, U13.25 (LON1)
/VGA2/LON2: C195.1, R70.2, U13.4 (LON2)
/VGA2/LOP1: C183.1, U13.24 (LOP1)
/VGA2/LOP2: C196.1, U13.5 (LOP2)
/VGA2/RCLMP: C176.1, R131.1, U13.11 (RCLMP)
/VGA2/VCM1: C181.1, C240.1, U13.20 (VCM1)
/VGA2/VCM2: C194.1, C236.1, U13.9 (VCM2)
/VGA2/VIN1: C182.2, U13.21 (VIN1)
/VGA2/VIN2: C195.2, U13.8 (VIN2)
/VGA2/VIP1: C183.2, U13.22 (VIP1)
/VGA2/VIP2: C196.2, U13.7 (VIP2)
/VGA3/ENB: R139.2, U14.18 (ENB)
/VGA3/FB1: C207.2, R74.1
/VGA3/FB2: C219.2, R75.1
/VGA3/HI~LO: R72.2, R73.1, U14.19 (HILO)
/VGA3/IN1_AC: C205.2, R121.1
/VGA3/IN2_AC: C213.2, R125.1
/VGA3/INH1: C206.1, C207.1, R121.2, U14.27 (INH1)
/VGA3/INH2: C215.1, C219.1, R125.2, U14.2 (INH2)
/VGA3/LMD1: C208.1, U14.28 (LMD1)
/VGA3/LMD2: C221.1, U14.1 (LMD2)
/VGA3/LON1: C210.1, R74.2, U14.25 (LON1)
/VGA3/LON2: C223.1, R75.2, U14.4 (LON2)
/VGA3/LOP1: C211.1, U14.24 (LOP1)
/VGA3/LOP2: C224.1, U14.5 (LOP2)
/VGA3/RCLMP: C204.1, R132.1, U14.11 (RCLMP)
/VGA3/VCM1: C209.1, C241.1, U14.20 (VCM1)
/VGA3/VCM2: C222.1, C237.1, U14.9 (VCM2)
/VGA3/VIN1: C210.2, U14.21 (VIN1)
/VGA3/VIN2: C223.2, U14.8 (VIN2)
/VGA3/VIP1: C211.2, U14.22 (VIP1)
/VGA3/VIP2: C224.2, U14.7 (VIP2)
GND: C1.2, C2.2, C3.2, C4.2, C5.2, C6.2, C7.2, C8.2, C11.2, C12.2, C13.2, C14.2, C27.1, C31.2, C32.2, C33.2, C34.2, C35.2, C36.2, C37.2, C42.2, C43.2, C44.2, C45.2, C46.2, C47.2, C48.2, C50.2, C52.2, C53.2, C56.2, C58.2, C59.2, C60.2, C61.2, C62.2, C64.2, C65.2, C66.2, C69.2, C70.2, C71.2, C72.2, C73.2, C74.2, C75.2, C76.2, C77.2, C80.2, C81.2, C82.2, C83.2, C84.2, C85.2, C86.2, C87.2, C88.2, C89.2, C90.2, C91.2, C92.2, C93.2, C94.2, C97.2, C98.2, C99.2, C100.2, C101.2, C102.2, C103.1, C107.2, C108.2, C109.2, C110.2, C111.2, C112.2, C113.2, C118.2, C119.2, C120.2, C121.2, C122.2, C123.2, C124.2, C125.2, C126.2, C127.2, C128.1, C132.2, C133.2, C134.2, C135.2, C136.2, C137.2, C138.2, C139.1, C143.1, C147.1, C151.1, C155.2, C157.2, C159.2, C160.2, C163.2, C165.2, C166.2, C167.2, C168.2, C169.2, C171.2, C172.2, C173.2, C176.2, C178.2, C180.2, C181.2, C184.2, C186.2, C187.2, C188.2, C189.2, C190.2, C192.2, C193.2, C194.2, C197.2, C198.2, C199.2, C200.2, C201.2, C202.2, C203.1, C204.2, C206.2, C208.2, C209.2, C212.2, C214.2, C215.2, C216.2, C217.2, C218.2, C220.2, C221.2, C222.2, C225.1, C229.2, C230.2, C231.2, C234.2, C235.2, C236.2, C237.2, C238.2, C239.2, C240.2, C241.2, C242.2, C243.2, C244.2, C245.2, C246.2, C247.2, C248.2, C249.2, C250.2, D1.1 (A), D1.4 (A), D2.1 (A), D2.4 (A), D5.1 (K), J1.2, J2.3, J3.2 (GND), J3.10 (GND), J4.1 (VeeT), J4.10 (VeeR), J4.11 (VeeR), J4.14 (VeeR), J4.17 (VeeT), J4.20 (VeeT), J4.CAGE, J5.2, J5.4, J5.6, J5.8, J5.10, J5.12, J5.14, J5.16, J5.P1, J5.P2, J6.3, J6.6, J6.9, J6.12, J7.2, J7.4, J7.6, J7.8, J7.14, J7.20, J7.22, J7.24, Q1.2 (S), Q2.2 (S), Q3.2 (S), Q4.2 (S), R9.2, R13.2, R26.2, R29.2, R31.2, R35.2, R63.2, R68.2, R73.2, R129.2, R130.2, R131.2, R132.2, SW1.1 (A), TP4.1 (1_1), TP6.1 (1_1), TP14.1 (1_1), U1.2 (GND), U2.2 (GND), U4.1x9 (GND), U4.1x10 (GND), U4.1x19 (GND), U4.1x20 (GND), U4.1x29 (GND), U4.1x30 (GND), U4.1x39 (GND), U4.1x40 (GND), U4.1x49 (GND), U4.1x50 (GND), U4.1x59 (GND), U4.1x60 (GND), U4.1x69 (GND), U4.1x70 (GND), U4.2x9 (GND), U4.2x10 (GND), U4.2x19 (GND), U4.2x20 (GND), U4.2x29 (GND), U4.2x30 (GND), U4.2x39 (GND), U4.2x40 (GND), U4.2x49 (GND), U4.2x50 (GND), U4.2x59 (GND), U4.2x60 (GND), U4.2x69 (GND), U4.2x70 (GND), U4.3x9 (GND), U4.3x10 (GND), U4.3x19 (GND), U4.3x20 (GND), U4.3x29 (GND), U4.3x30 (GND), U4.3x39 (GND), U4.3x40 (GND), U4.3x49 (GND), U4.3x50 (GND), U4.3x59 (GND), U4.3x60 (GND), U4.3x69 (GND)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
